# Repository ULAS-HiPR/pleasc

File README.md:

# Pléasc

Pléasc is the recovery-deployment node in [Ogma](https://sean-osullivan.com/projects/ogma/), the University of Limerick Aeronautics Society's modular avionics stack for high-powered rocketry.

## Role

- Monitors continuity on four deployment channels.
- Controls four recovery outputs from an STM32F072.
- Uses guarded arm and fire commands over the 500 kbit/s CAN bus.
- Keeps recovery outputs in defined safe states unless the complete command path is valid.

## Repository

- `hardware/` - KiCad design and manufacturing outputs.
- `firmware/` - embedded firmware, continuity/deployment probes, and tests.

## Status

Rev 1 firmware and hardware bring-up continue on [`ogma/flight-hardening`](https://github.com/ULAS-HiPR/pleasc/tree/ogma/flight-hardening). Release-candidate firmware builds and software tests pass, but hardware-in-the-loop validation is still underway. Pléasc is not yet flight-proven.

## Manufacturing support

Rev 1 PCB fabrication was sponsored through [EasyEDA Education](https://easyeda.com/education) and manufactured by [JLCPCB](https://jlcpcb.com/). The board was designed in KiCad and imported into EasyEDA Pro for the sponsorship and manufacturing workflow.

## More information

See the [Ogma project write-up](https://sean-osullivan.com/projects/ogma/) for the complete stack, bring-up work, and current status.

> [!WARNING]
> This project is archived, and is no longer actively supported.
> Contact us for more details.

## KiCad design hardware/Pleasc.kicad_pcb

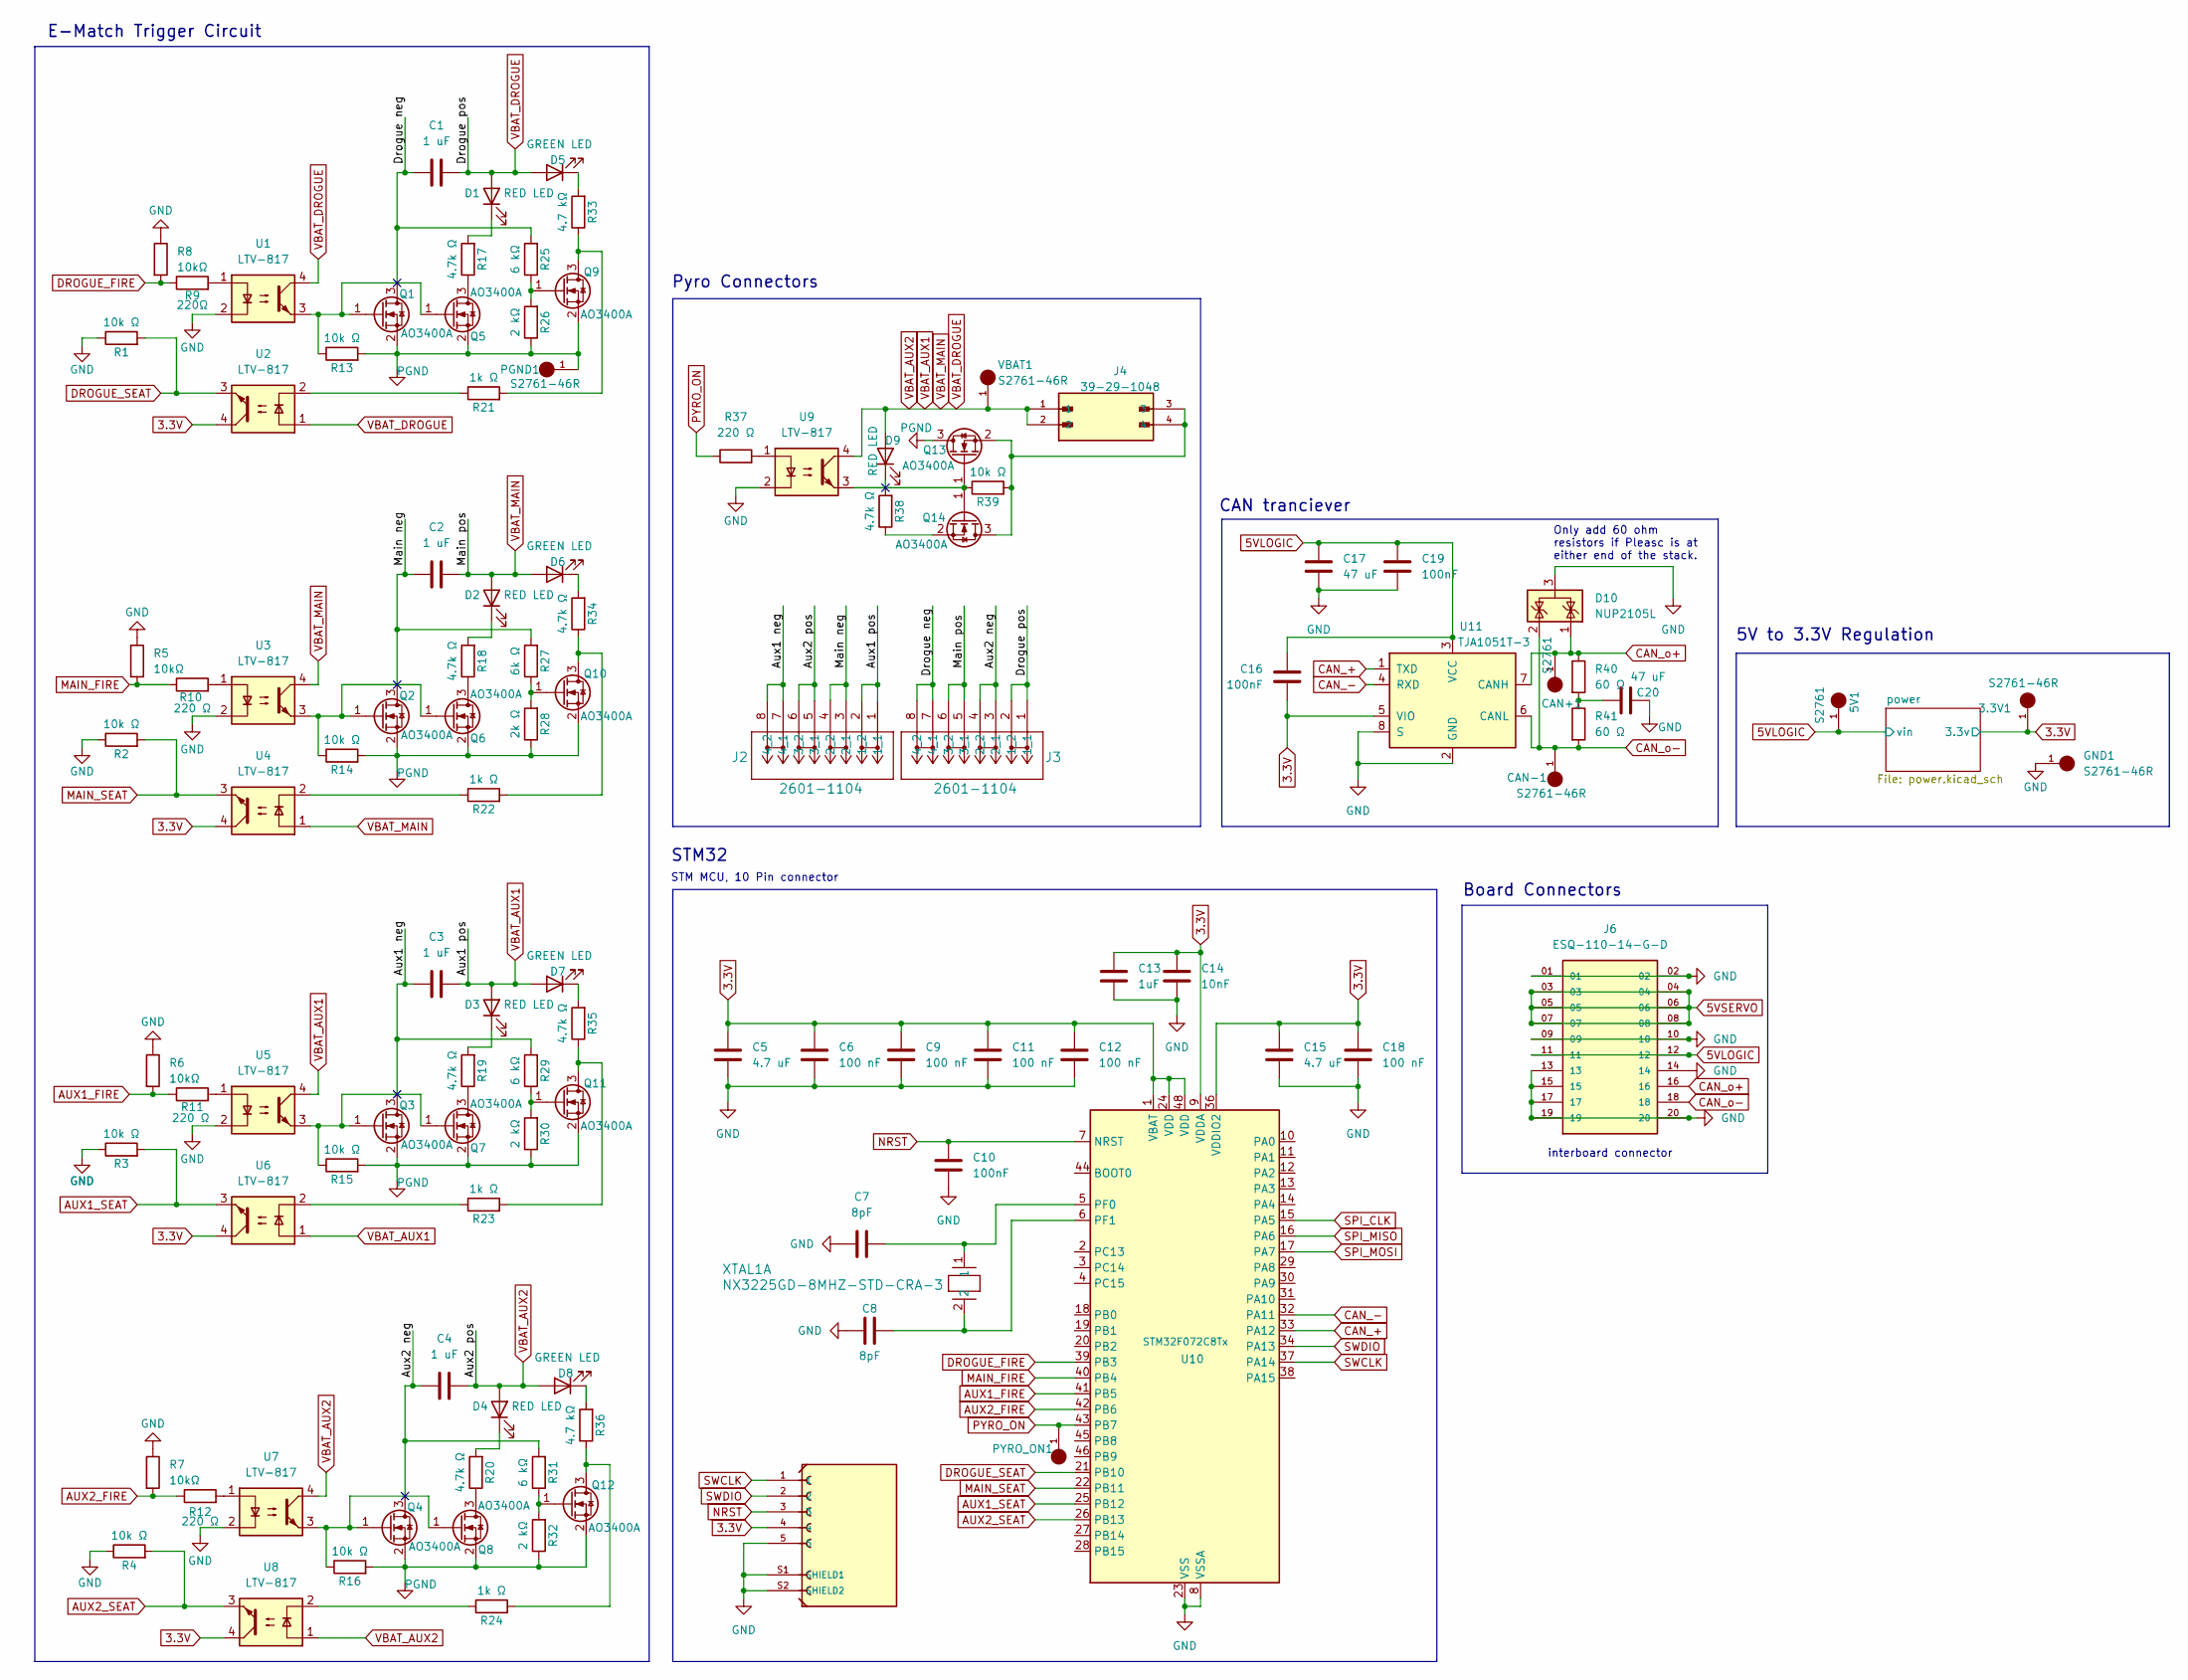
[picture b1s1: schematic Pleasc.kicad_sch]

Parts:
3.3V1: S2761-46R; HARWIN_S2761-46R; PARTREV 1
5V1: S2761; HARWIN_S2761-46R; PARTREV 1
C1, C2, C3, C4: 1 uF; C_0402_1005Metric
C5, C15: 4.7 uF; C_0402_1005Metric
C6, C9, C11, C12, C18: 100 nF; C_0402_1005Metric
C7, C8: 8pF; C_0402_1005Metric
C10, C16, C19: 100nF; C_0402_1005Metric
C13: 1uF; C_0402_1005Metric
C14: 10nF; C_0603_1608Metric
C17, C20: 47 uF; C_0603_1608Metric
CAN+1: S2761; HARWIN_S2761-46R; PARTREV 1
CAN-1: S2761-46R; HARWIN_S2761-46R; PARTREV 1
D1, D2, D3, D4, D9: RED LED; LED_0402_1005Metric
D5, D6, D7, D8: GREEN LED; LED_0402_1005Metric
D10: NUP2105L; SOT-23
GND1: S2761-46R; HARWIN_S2761-46R; PARTREV 1
J1: 5023860570; MOLEX_5023860570; PARTREV F
J2, J3: 2601-1104; CONN4_2601-1104_WAG
J4: 39-29-1048; MOLEX_39-29-1048
J6: ESQ-110-14-G-D; SAMTEC_ESQ-110-14-G-D; PARTREV NA
PGND1: S2761-46R; HARWIN_S2761-46R; PARTREV 1
PYRO_ON1: S2761-46R; HARWIN_S2761-46R; PARTREV 1
Q1, Q2, Q3, Q4, Q5, Q6, Q7, Q8, Q9, Q10, Q11, Q12, Q13, Q14: AO3400A; SOT-23
R1, R2, R3, R4, R13, R14, R15, R16, R39: 10k Ω; R_0402_1005Metric
R5, R6, R7, R8: 10kΩ; R_0402_1005Metric
R9: 220Ω; R_0402_1005Metric
R10, R11, R12, R37: 220 Ω; R_0402_1005Metric
R17, R18, R19, R20, R34, R35, R38: 4.7k Ω; R_0402_1005Metric
R21, R22, R23, R24: 1k Ω; R_0402_1005Metric
R25, R29, R31: 6 kΩ; R_0402_1005Metric
R26, R30, R32: 2 kΩ; R_0402_1005Metric
R27: 6k Ω; R_0402_1005Metric
R28: 2k Ω; R_0402_1005Metric
R33, R36: 4.7 kΩ; R_0402_1005Metric
R40, R41: 60 Ω; R_0402_1005Metric
U1, U2, U3, U4, U5, U6, U7, U8, U9: LTV-817; SO4_TOS
U10: STM32F072C8Tx; LQFP-48_7x7mm_P0.5mm
U11: TJA1051T-3; SOIC-8_3.9x4.9mm_P1.27mm
VBAT1: S2761-46R; HARWIN_S2761-46R; PARTREV 1
XTAL1: NX3225GD-8MHZ-STD-CRA-3; XTAL_NX3225GD-8MHZ-STD-CRA-3_NDK

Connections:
3.3V: 3.3V1.1, C5.1, C6.1, C9.1, C11.1, C12.1, C13.1, C14.1, C15.1, C16.1, C18.1, J1.4, U2.4, U4.4, U6.4, U8.4, U10.1 (VBAT), U10.9 (VDDA), U10.24 (VDD), U10.36 (VDDIO2), U10.48 (VDD), U11.5 (VIO); also elsewhere on the board
5VLOGIC: 5V1.1, C16.2, C17.1, C19.1, J6.11, J6.12, U11.3 (VCC); also elsewhere on the board
5VSERVO: J6.03, J6.04, J6.05, J6.06, J6.07, J6.08
/Aux1 neg: C3.2, J2.7 (4_1), J2.8 (4_2), Q3.3 (D), R29.2
/Aux2 neg: C4.2, J3.3 (2_1), J3.4 (2_2), Q4.3 (D), R31.2
/Drogue neg: C1.2, J3.7 (4_1), J3.8 (4_2), Q1.3 (D), R25.2
/Main neg: C2.2, J2.3 (2_1), J2.4 (2_2), Q2.3 (D), R27.2
AUX1_FIRE: R6.2, R11.1, U10.41 (PB5)
AUX1_SEAT: R3.2, U6.3, U10.25 (PB12)
AUX2_FIRE: R7.2, R12.1, U10.42 (PB6)
AUX2_SEAT: R4.2, U8.3, U10.26 (PB13)
CAN_+: U10.33 (PA12), U11.1 (TXD)
CAN_-: U10.32 (PA11), U11.4 (RXD)
CAN_o+: CAN+1.1, D10.1 (K), J6.16, R40.1, U11.7 (CANH); also elsewhere on the board
CAN_o-: CAN-1.1, D10.2 (K), J6.18, R41.2, U11.6 (CANL); also elsewhere on the board
DROGUE_FIRE: R8.2, R9.1, U10.39 (PB3)
DROGUE_SEAT: R1.2, U2.3, U10.21 (PB10)
GND: C5.2, C6.2, C7.1, C8.1, C9.2, C10.2, C11.2, C12.2, C13.2, C14.2, C15.2, C17.2, C18.2, C19.2, C20.2, D10.3 (A), GND1.1, J1.5, J1.S1 (SHIELD1), J1.S2 (SHIELD2), J6.01, J6.02, J6.09, J6.10, J6.13, J6.14, J6.15, J6.17, J6.19, J6.20, R1.1, R2.1, R3.1, R4.1, R5.1, R6.1, R7.1, R8.1, U1.2, U3.2, U5.2, U7.2, U9.2, U10.8 (VSSA), U10.23 (VSS), U10.35 (VSS), U10.47 (VSS), U11.2 (GND), U11.8 (S); also elsewhere on the board
MAIN_FIRE: R5.2, R10.1, U10.40 (PB4)
MAIN_SEAT: R2.2, U4.3, U10.22 (PB11)
NRST: C10.1, J1.3, U10.7 (NRST)
unnamed: C20.1, R40.2, R41.1
unnamed: D1.1 (K), R17.2
unnamed: D2.1 (K), R18.2
unnamed: D3.1 (K), R19.2
unnamed: D4.1 (K), R20.2
unnamed: D5.1 (K), R33.2
unnamed: D6.1 (K), R34.2
unnamed: D7.1 (K), R35.2
unnamed: D8.1 (K), R36.2
unnamed: Q1.1 (G), Q5.1 (G), R13.1, U1.3
unnamed: Q2.1 (G), Q6.1 (G), R14.1, U3.3
unnamed: Q3.1 (G), Q7.1 (G), R15.1, U5.3
unnamed: Q4.1 (G), Q8.1 (G), R16.1, U7.3
unnamed: Q5.3 (D), R17.1
unnamed: Q6.3 (D), R18.1
unnamed: Q7.3 (D), R19.1
unnamed: Q8.3 (D), R20.1
unnamed: Q9.3 (D), R21.2, R33.1
unnamed: Q9.1 (G), R25.1, R26.2
unnamed: Q10.3 (D), R22.2, R34.1
unnamed: Q10.1 (G), R27.1, R28.2
unnamed: Q11.3 (D), R23.2, R35.1
unnamed: Q11.1 (G), R29.1, R30.2
unnamed: Q12.3 (D), R24.2, R36.1
unnamed: Q12.1 (G), R31.1, R32.2
unnamed: Q13.1 (G), Q14.1 (G), R39.1, U9.3
unnamed: J4.3, J4.4, Q13.2 (S), Q14.3 (D), R39.2
unnamed: Q14.2 (S), R38.1
unnamed: R9.2, U1.1
unnamed: R10.2, U3.1
unnamed: R11.2, U5.1
unnamed: R12.2, U7.1
unnamed: R21.1, U2.2
unnamed: R22.1, U4.2
unnamed: R23.1, U6.2
unnamed: R24.1, U8.2
unnamed: R37.2, U9.1
unnamed: C7.2, U10.5 (PF0), XTAL1.1
unnamed: C8.2, U10.6 (PF1), XTAL1.2
PGND: PGND1.1, Q1.2 (S), Q2.2 (S), Q3.2 (S), Q4.2 (S), Q5.2 (S), Q6.2 (S), Q7.2 (S), Q8.2 (S), Q9.2 (S), Q10.2 (S), Q11.2 (S), Q12.2 (S), Q13.3 (D), R13.2, R14.2, R15.2, R16.2, R26.1, R28.1, R30.1, R32.1; also elsewhere on the board
PYRO_ON: PYRO_ON1.1, R37.1, U10.43 (PB7); also elsewhere on the board
SPI_CLK: U10.15 (PA5)
SPI_MISO: U10.16 (PA6)
SPI_MOSI: U10.17 (PA7)
SWCLK: J1.1, U10.37 (PA14)
SWDIO: J1.2, U10.34 (PA13)
VBAT_AUX1: C1.1, C2.1, C3.1, C4.1, D1.2 (A), D2.2 (A), D3.2 (A), D4.2 (A), D5.2 (A), D6.2 (A), D7.2 (A), D8.2 (A), D9.2 (A), J2.1 (1_1), J2.2 (1_2), J2.5 (3_1), J2.6 (3_2), J3.1 (1_1), J3.2 (1_2), J3.5 (3_1), J3.6 (3_2), J4.1, J4.2, U1.4, U2.1, U3.4, U4.1, U5.4, U6.1, U7.4, U8.1, U9.4, VBAT1.1; also elsewhere on the board

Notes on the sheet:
5V to 3.3V Regulation
STM32
CAN tranciever
E-Match Trigger Circuit
STM MCU, 10 Pin connector
Pyro Connectors
interboard connector
Board Connectors
Only add 60 ohm resistors if Pleasc is at either end of the stack.

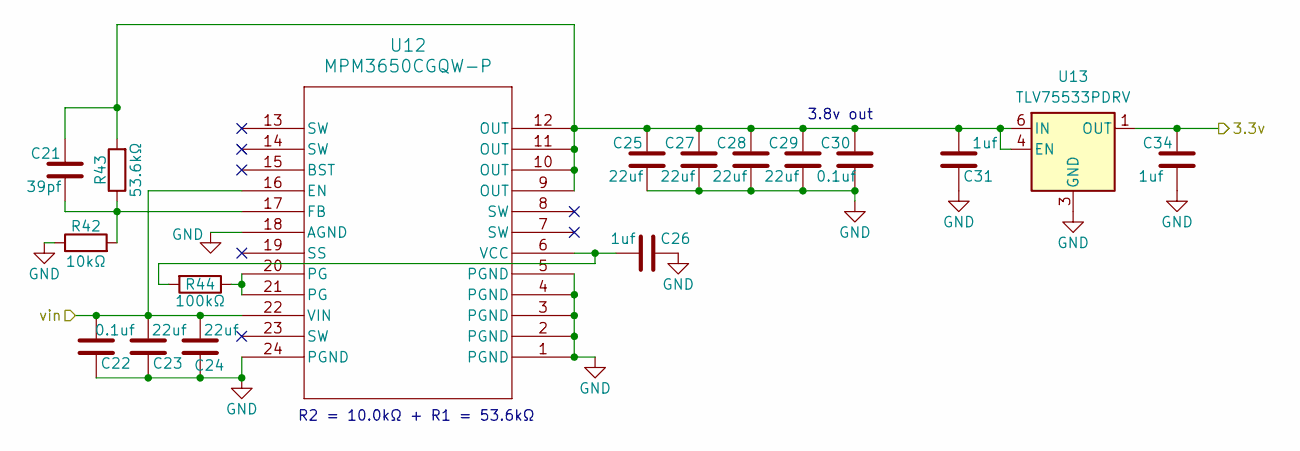
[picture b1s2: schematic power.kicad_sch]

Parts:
C21: 39pf; C_0402_1005Metric
C22, C30: 0.1uf; C_0402_1005Metric
C23, C24, C25, C27, C28, C29: 22uf; C_0603_1608Metric
C26, C31, C34: 1uf; C_0402_1005Metric
R42: 10kΩ; R_0402_1005Metric
R43: 53.6kΩ; R_0402_1005Metric
R44: 100kΩ; R_0402_1005Metric
U12: MPM3650CGQW-P; QFN-24_MPM3650_MNP
U13: TLV75533PDRV; WSON-6-1EP_2x2mm_P0.65mm_EP1x1.6mm

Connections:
3.3V: C34.1, U13.1 (OUT); also elsewhere on the board
5VLOGIC: C22.2, C23.2, C24.2, U12.16 (EN), U12.22 (VIN); also elsewhere on the board
GND: C22.1, C23.1, C24.1, C25.2, C26.1, C27.2, C28.2, C29.2, C30.2, C31.1, C34.2, R42.1, U12.1 (PGND), U12.2 (PGND), U12.3 (PGND), U12.4 (PGND), U12.5 (PGND), U12.18 (AGND), U12.24 (PGND), U13.3 (GND), U13.7 (GND); also elsewhere on the board
unnamed: R44.1, U12.20 (PG), U12.21 (PG)
unnamed: C21.2, R42.2, R43.1, U12.17 (FB)
unnamed: C26.2, R44.2, U12.6 (VCC)
unnamed: C21.1, C25.1, C27.1, C28.1, C29.1, C30.1, C31.2, R43.2, U12.9 (OUT), U12.10 (OUT), U12.11 (OUT), U12.12 (OUT), U13.4 (EN), U13.6 (IN)

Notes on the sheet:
3.8v out
R2 = 10.0kΩ + R1 = 53.6kΩ

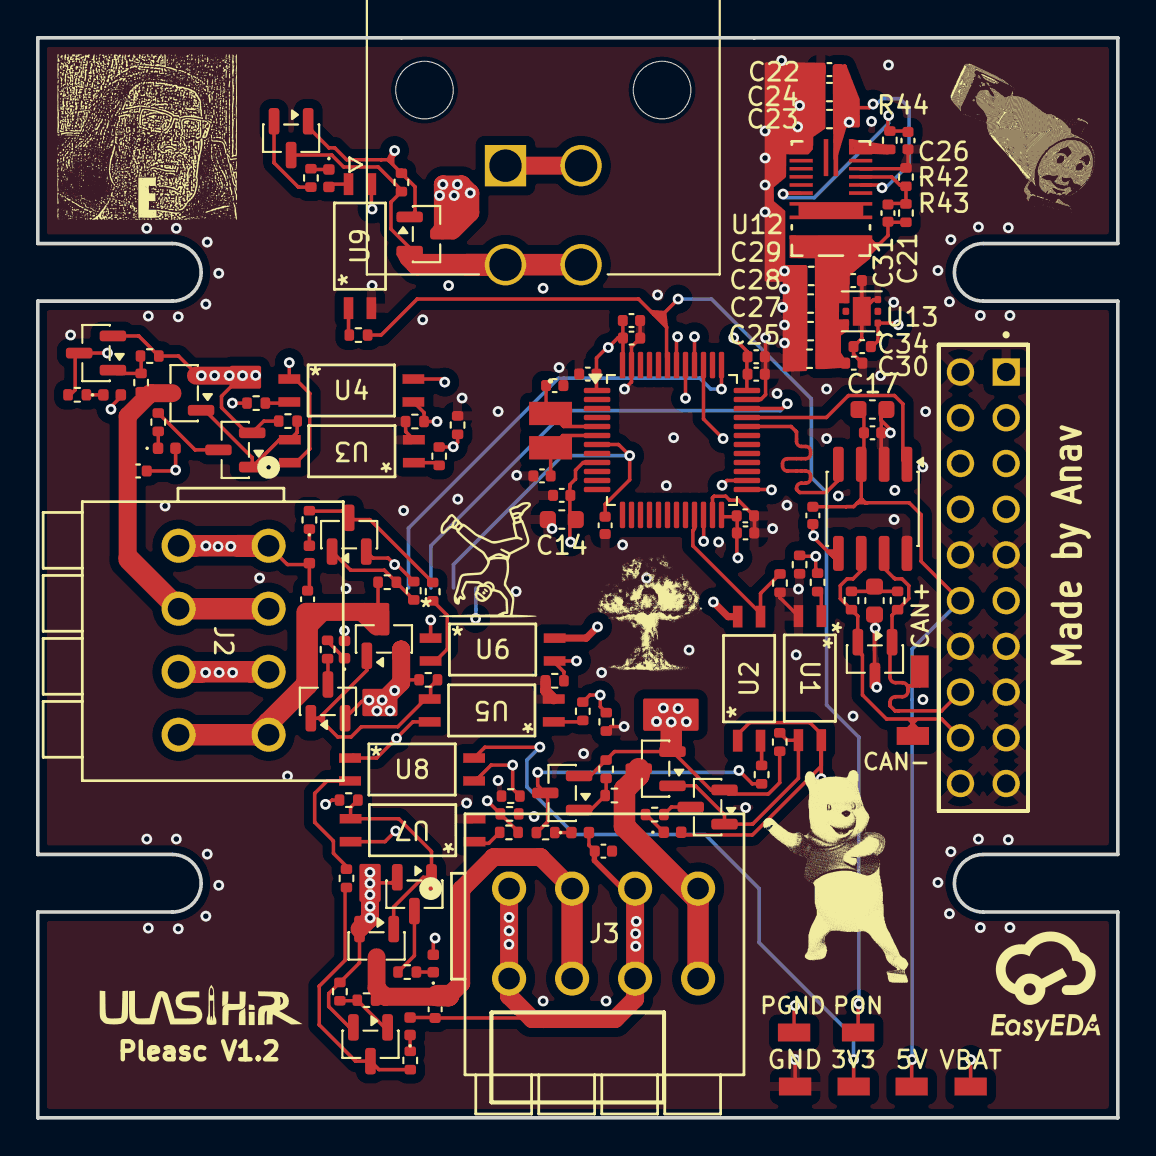
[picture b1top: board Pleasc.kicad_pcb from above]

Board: 6 copper layers, 60.0 x 60.0 mm, 127 parts (1 on the bottom side), 69 nets.

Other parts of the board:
3V3: S2761-46R; HARWIN_S2761-46R
5V: S2761; HARWIN_S2761-46R
CAN+: S2761; HARWIN_S2761-46R
CAN-: S2761-46R; HARWIN_S2761-46R
GND: S2761-46R; HARWIN_S2761-46R
PGND: S2761-46R; HARWIN_S2761-46R
PON: S2761-46R; HARWIN_S2761-46R
VBAT: S2761-46R; HARWIN_S2761-46R

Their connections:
3.3V: 3V3.1; also elsewhere on the board
5VLOGIC: 5V.1; also elsewhere on the board
CAN_o+: CAN+.1; also elsewhere on the board
CAN_o-: CAN-.1; also elsewhere on the board
GND: GND.1; also elsewhere on the board
PGND: PGND.1; also elsewhere on the board
PYRO_ON: PON.1; also elsewhere on the board
VBAT_AUX1: VBAT.1; also elsewhere on the board

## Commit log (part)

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2026-01-27 Schematic complete, components layed out on the PCB
2026-01-29 All 4 Pyros circuits routed
2026-01-31 Final draft V1.0
2026-01-31 added can crystal
2026-02-03 3d model made
2026-02-09 Version 1.2
2026-02-10 visual changes
2026-02-10 model
2026-02-11 minor stuff
2026-02-22 cleaning
2026-02-22 ready for review
2026-02-23 ready for review the twost
2026-02-27 ready to go, nearly
2026-03-01 ready 2 order
2026-03-05 Adding all inital files
2026-03-05 removing ds store again
2026-03-31 hardware done
2026-05-18 feat(sil): comheadan + linux platform config
